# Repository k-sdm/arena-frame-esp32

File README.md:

# Arena Frame on an ESP32-S3

A port of [arena-frame](https://github.com/k-sdm/arena-frame) (Raspberry Pi) to an
ESP32-S3 driving a Pimoroni Inky Impression 7.3" Spectra 6 panel. It connects to WiFi,
pulls blocks from an Are.na channel, fits and dithers images to the panel's six inks,
and draws the block title and channel line beneath.

## Layout

    device/        MicroPython modules that live on the board
      inky.py      panel driver (SPI, full refresh ~29 s)
      image.py     fetch, JPEG decode, scale, Floyd-Steinberg dither, rotate
      render.py    portrait 480x800 canvas, text layout, overlay, rotation
      font.py      1bpp bitmap fonts built from ABC Areal
      arena.py     Are.na API v3 client
      wifi.py      station-mode connection
      main.py      scheduler loop (deployed as frame.py)
      main_boot.py launcher (deployed as main.py, runs on power-up)
      fonts/       generated bitmap fonts
    config-tool/   Web Serial setup page (Chrome/Edge) — configure over USB
    build_font.py  renders a TTF into the bitmap font format
    mpr            mpremote wrapper, finds the board automatically
    flash           esptool wrapper for firmware

## Panels

Chosen in the setup page, stored as `panel` in config.json:

| Setting | Panel | Pixels | Controller | State |
|---|---|---|---|---|
| `7.3` | Inky Impression 7.3" | 800 x 480 | EL673 | tested |
| `4.0` | Inky Impression 4" | 600 x 400 | E640 | same command set, untested |
| `13.3` | Inky Impression 13.3" | 1600 x 1200 | EL133UF1 | untested, needs a second chip-select |

The 4" differs from the 7.3" only in the resolution bytes and one pre-refresh value.
The 13.3" is a different controller: two of them, each driving 600 of the 1200 columns,
at 10 MHz with a refresh around 65 s. It needs a second CS line (Pi header pins 37 and
36, BCM 26 and 16) — the carrier board wires one CS, so that panel needs a board revision.
A later revision is to read the panel's EEPROM and pick the size itself.

## Wiring

| Inky header pin | Signal | ESP32-S3 |
|---|---|---|
| 19 | MOSI | GPIO 11 |
| 23 | SCLK | GPIO 12 |
| 24 | Chip select | GPIO 10 |
| 15 | Data/command | GPIO 9 |
| 13 | Reset | GPIO 8 |
| 11 | Busy | GPIO 7 |
| 2 / 1 / 6 | 5V / 3V3 / GND | 5V / 3V3 / GND |

MISO is unused. Avoid GPIO 26-37 (flash and octal PSRAM), 0/3/45/46 (strapping),
19/20 (USB), 43/44 (UART) and 38 (RGB LED).

## Provisioning a fresh board

    ./provision              # firmware, code, fonts, boot launcher
    ./provision --code-only  # push code changes, keeping settings

It fetches the tools and firmware on first run, erases and flashes the chip, copies
everything across and checks what landed. Then set WiFi and the channel from
`config-tool/index.html`. Pass `PORT=/dev/cu.usbmodem...` to choose a board.

## Firmware

MicroPython with a JPEG decoder: the prebuilt
[mp_jpeg](https://github.com/cnadler86/mp_jpeg) build for `ESP32_GENERIC_S3-SPIRAM_OCT`.
Flash it over the board's UART port (the native USB port will not enter download mode):

    ./flash firmware/firmware.bin

## Deploying the code

    ./mpr fs cp device/*.py :
    ./mpr fs cp device/main.py :frame.py
    ./mpr fs cp device/main_boot.py :main.py
    ./mpr fs mkdir fonts && ./mpr fs cp device/fonts/*.bin :fonts/

Then open `config-tool/index.html` in Chrome (over https or localhost) to set WiFi,
the channel and display options. Settings live in `config.json` on the board; position
in the channel is kept in `state.json`.

## Notes on the panel

This is the 2026 "AC waveform" Spectra 6 panel (EEPROM variant 26). A full refresh takes
about 29 s. Partial refresh via the 0x83 window register does not confine the waveform on
this revision — the whole panel cycles — so the frame uses full refreshes only.

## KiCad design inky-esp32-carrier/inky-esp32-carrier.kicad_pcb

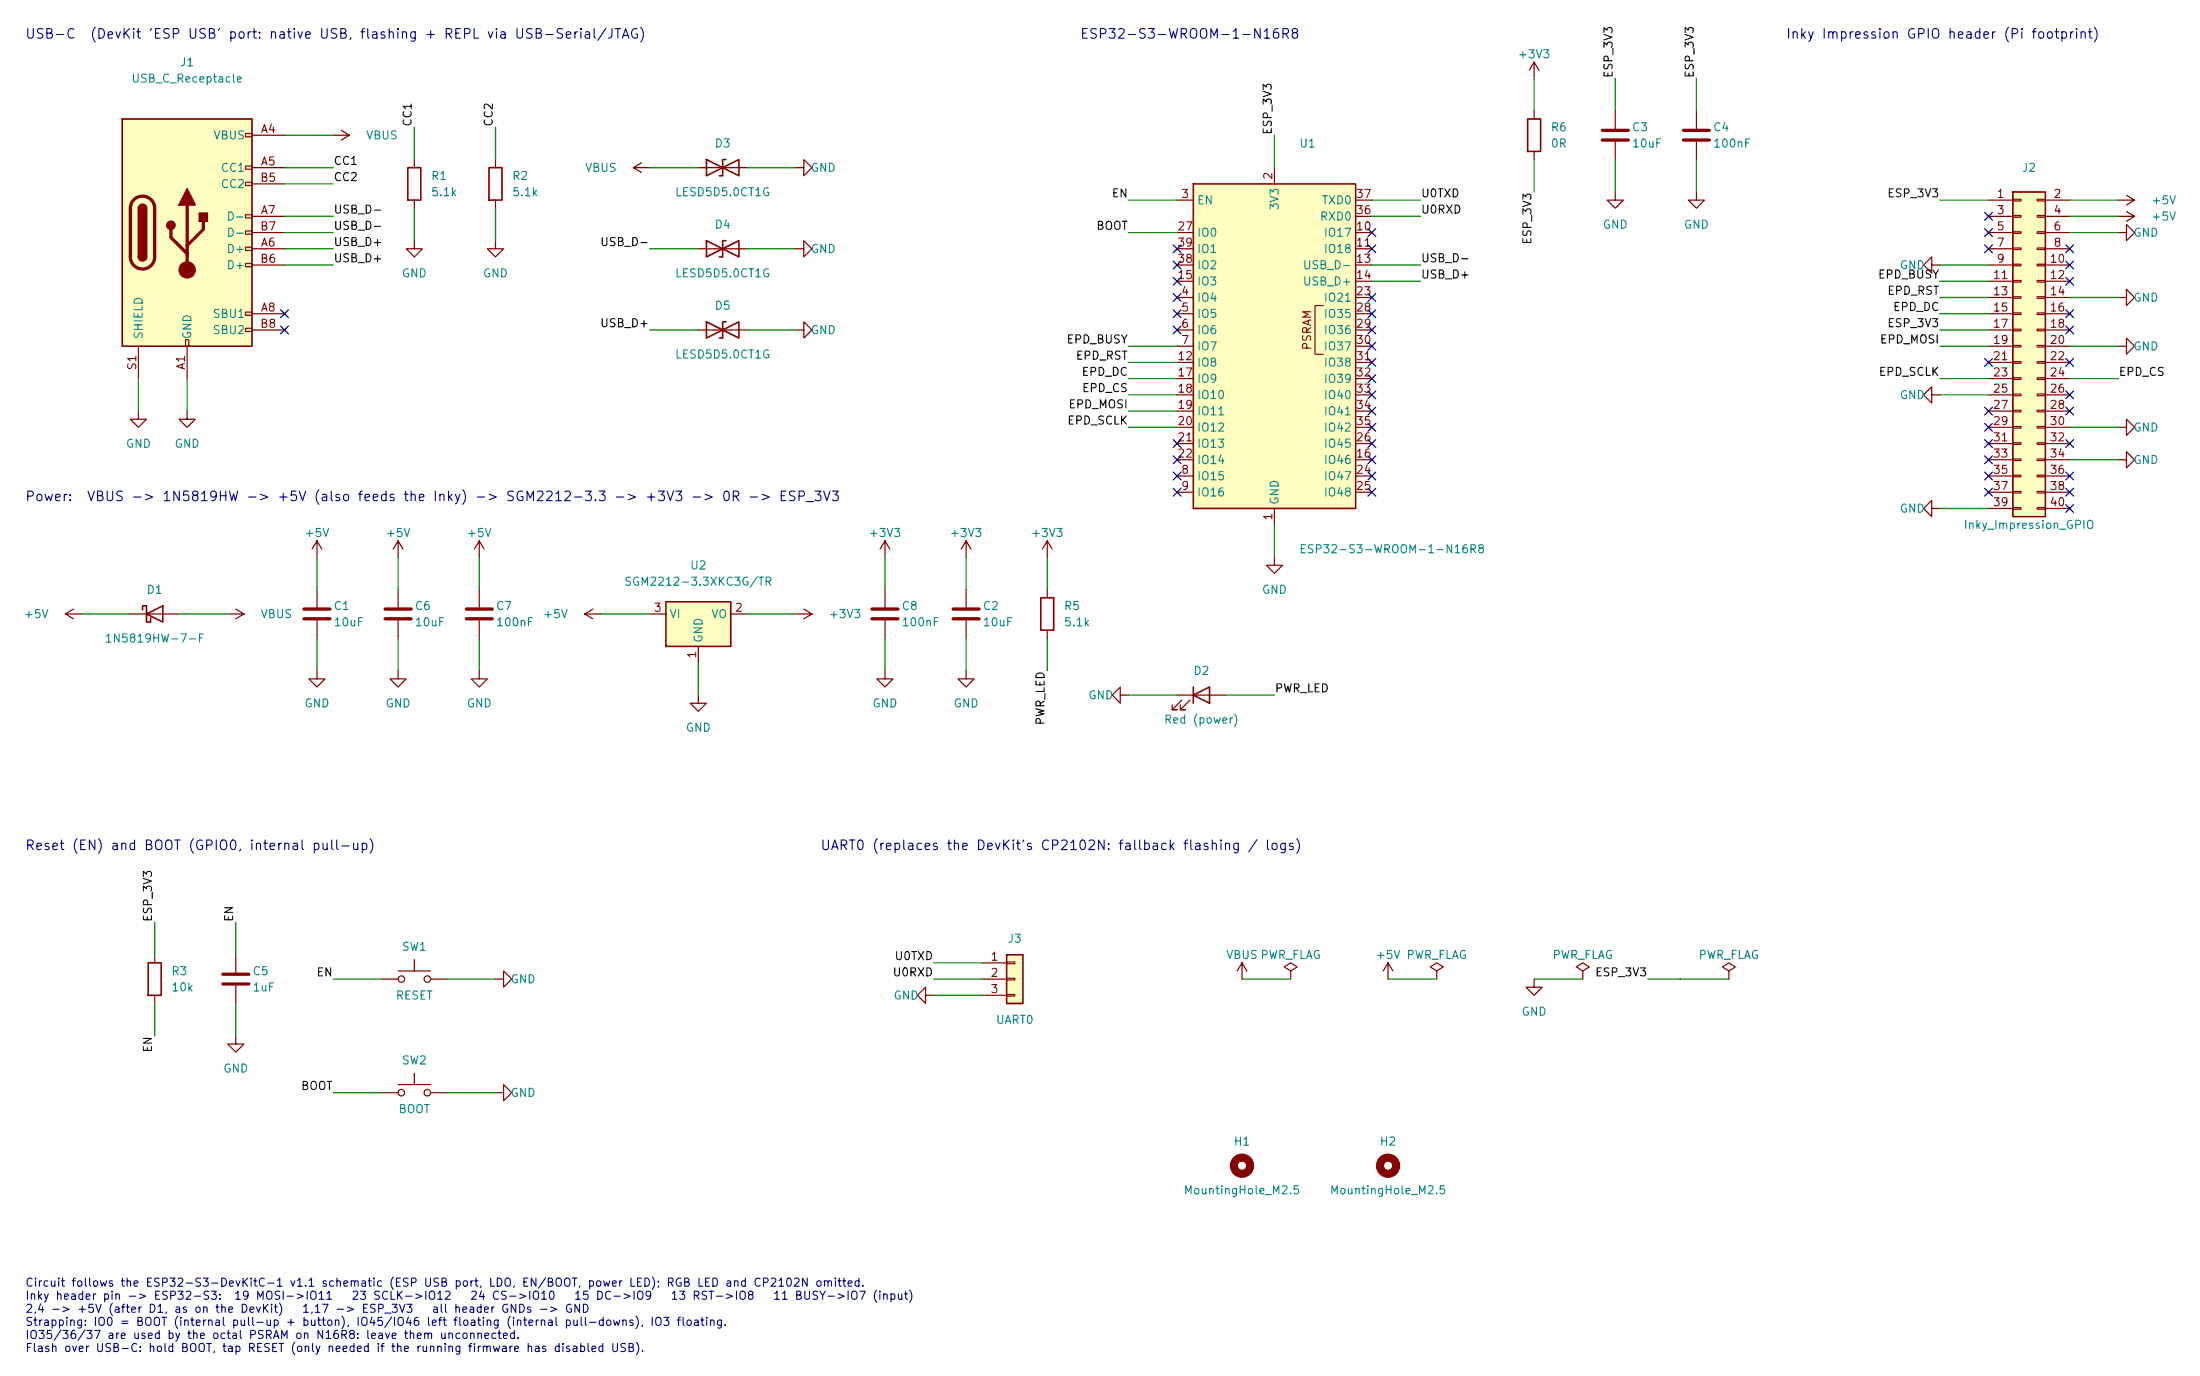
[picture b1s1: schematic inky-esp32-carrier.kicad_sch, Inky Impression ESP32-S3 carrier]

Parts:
C1, C2, C3, C6: 10uF; C_0805_2012Metric
C4, C7, C8: 100nF; C_0603_1608Metric
C5: 1uF; C_0603_1608Metric
D1: 1N5819HW-7-F; D_SOD-123
D2: Red (power); LED_0603_1608Metric
D3, D4, D5: LESD5D5.0CT1G; D_SOD-523
H1, H2: MountingHole_M2.5; MountingHole_2.7mm_M2.5
J1: USB_C_Receptacle; USB_C_Receptacle_HRO_TYPE-C-31-M-12
J2: Inky_Impression_GPIO; PinHeader_2x20_P2.54mm_Vertical
J3: UART0; PinHeader_1x03_P2.54mm_Vertical
R1, R2, R5: 5.1k; R_0603_1608Metric
R3: 10k; R_0603_1608Metric
R6: 0R; R_0603_1608Metric
SW1: RESET; SW_Push_1P1T_XKB_TS-1187A
SW2: BOOT; SW_Push_1P1T_XKB_TS-1187A
U1: ESP32-S3-WROOM-1-N16R8; ESP32-S3-WROOM-1_BodyCourtyard
U2: SGM2212-3.3XKC3G/TR; SOT-223-3_TabPin2

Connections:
+3V3: C2.1, C8.1, R5.1, R6.1, U2.2 (VO)
+5V: C1.1, C6.1, C7.1, D1.1 (K), J2.2, J2.4, U2.3 (VI)
/BOOT: SW2.1, U1.27 (IO0)
/CC1: J1.A5 (CC1), R1.1
/CC2: J1.B5 (CC2), R2.1
/EN: C5.1, R3.2, SW1.1, U1.3 (EN)
/EPD_BUSY: J2.11, U1.7 (IO7)
/EPD_CS: J2.24, U1.18 (IO10)
/EPD_DC: J2.15, U1.17 (IO9)
/EPD_MOSI: J2.19, U1.19 (IO11)
/EPD_RST: J2.13, U1.12 (IO8)
/EPD_SCLK: J2.23, U1.20 (IO12)
/ESP_3V3: C3.1, C4.1, J2.1, J2.17, R3.1, R6.2, U1.2 (3V3)
/PWR_LED: D2.2 (A), R5.2
/U0RXD: J3.2, U1.36 (RXD0)
/U0TXD: J3.1, U1.37 (TXD0)
/USB_D+: D5.1 (A1), J1.A6 (D+), J1.B6 (D+), U1.14 (USB_D+)
/USB_D-: D4.1 (A1), J1.A7 (D-), J1.B7 (D-), U1.13 (USB_D-)
GND: C1.2, C2.2, C3.2, C4.2, C5.2, C6.2, C7.2, C8.2, D2.1 (K), D3.2 (A2), D4.2 (A2), D5.2 (A2), J1.A1 (GND), J1.A12 (GND), J1.B1 (GND), J1.B12 (GND), J1.S1 (SHIELD), J2.6, J2.9, J2.14, J2.20, J2.25, J2.30, J2.34, J2.39, J3.3, R1.2, R2.2, SW1.2, SW2.2, U1.1 (GND), U1.40 (GND), U1.41 (GND), U2.1 (GND)
VBUS: D1.2 (A), D3.1 (A1), J1.A4 (VBUS), J1.A9 (VBUS), J1.B4 (VBUS), J1.B9 (VBUS)

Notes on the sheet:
USB-C (DevKit 'ESP USB' port: native USB, flashing + REPL via USB-Serial/JTAG)
Power: VBUS -> 1N5819HW -> +5V (also feeds the Inky) -> SGM2212-3.3 -> +3V3 -> 0R -> ESP_3V3
ESP32-S3-WROOM-1-N16R8
Reset (EN) and BOOT (GPIO0, internal pull-up)
UART0 (replaces the DevKit's CP2102N: fallback flashing / logs)
Inky Impression GPIO header (Pi footprint)
Circuit follows the ESP32-S3-DevKitC-1 v1.1 schematic (ESP USB port, LDO, EN/BOOT, power LED); RGB LED and CP2102N omitted. Inky header pin -> ESP32-S3: 19 MOSI->IO11 23 SCLK->IO12 24 CS->IO10 15 DC->IO9 13 RST->IO8 11 BUSY->IO7 (input) 2,4 -> +5V (after D1, as on the DevKit) 1,17 -> ESP_3V3 all he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

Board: 2 copper layers, 27 parts (1 on the bottom side), 20 nets, no tracks yet.
